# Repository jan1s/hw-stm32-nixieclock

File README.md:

# hw-nixieclock

The firmware running on the clock: [Firmware](https://github.com/jan1s/fw-clock)

A small Gist to configure a STM32 toolchain on Mac: [Toolchain](https://jan1s.github.io)

To flash the controller a STM32 Programmer is needed, just get the cheapest one from China.

## Initial Configuration

Before the clock will actually start working, it is necessary to set the type:

```bash
nixie_settype <type>
nixie_settype <type(0-4)>
```

Where `<type>` is a number defining the nixie clock type.

1. ZM1000
2. Z570M, IN-8
3. ZM1325
4. IN-14, ZM1020

It is also required to set the mode of operation:

```bash
nixie_setmode <mode>
nixie_setmode <mode(0=NONE|1=HHMMSS|2=HHMM|3=MMSS|4=YYYY)>
```

Where `<mode>` is a number defining the nixie operation mode.

1. HH:MM:SS
2. HH:MM
3. MM:SS
4. YYYY

## PCBs

The clock has seperate control and display pcbs. Those pcbs do not only form a basic case for the electronics, but also allow for flexible use with different tubes.

[Control PCBs](layout/control)

[Display PCBs](layout/display)

[Source PCBs](layout/source)

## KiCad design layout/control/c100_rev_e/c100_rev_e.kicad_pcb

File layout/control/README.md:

# Control PCBs

## c100

rev. a

In the first revision of the PCBs are some minor errors. (This is the version from the 32C3 workshop)
Find detailed pictures of the first prototype [here](../../docu/detail_c100_rev_a).

* A pullup resistor is missing on the USB data lines
* LED silkscreen missing, they are on the right of the controller

rev. b

## c150

rev. a

### control BOM
| Identifier | Type/Value | Quantity | [Reichelt][reichelt] | [Digikey][digikey] | Comment |
| :---        | :---        | :---      | :---         | :---      | :---     |
| R1, R2, R3, R4 | 33 Ω | 4 | SMD-0603 33 | 311-33GRCT-ND |
| R12, R13 | 1 kΩ | 2 | SMD-0603 1,00K | 311-1.0KGRCT-ND |
| C1, C2, C13, C14 | 10 pF | 4 | NPO-G0603 10P |  |
| C7, C8 | 10 nF | 2 | X7R-G0603 10N |  |
| C18, C19, C20, C21 | 100 nF | 4 | X7R-G0603 100N |  |
| C3, C5, C6, C10, C11 | 10 µF | 5 | X5R-G0603 10/6 |  |
| FB1 | Ferrite Bead | 1 | BLM18AG 121 | 490-1011-1-ND |
| Y1 | 8MHz | 1 | - | 535-10630-1-ND |
| Y2 | 32kHz | 1 | 32,768 PGD-9 | 535-9542-1-ND |
| LED1 | LED green | 1 | LG L29K |  |
| LED2 | LED white | 1 | LW L283 | |
| BAT1 | Batteryholder | 1 | - | BC501SM-ND | c100 |
| BAT1 | Batteryholder | 1 | KZH 20SMD-2 | - | c150 |
| BAT | CR 1220 | 1 | CR 1220 VAR | SY033-ND |
| SW1 | Tact Switch Top | 1 | - | EG2531CT-ND |
| J1 | 2x5 Socket | 1 | - | A100866TR-ND, S5714-ND |
| J2 | USB Jack | 1 | USB BWM SMD | 151-1206-1-ND |
| IC1 | STM32F103C8T6 | 1 | STM32 F103C8T6 | 497-6063-ND |
| IC2, IC6 | LP2985 | 1 | LP 2985 IM5-3,3 |  |
| IC3, IC4 | USBLC6-2 | 1 | - | 497-5235-1-ND |

### power supply BOM
| Identifier | Type/Value | Quantity | [Reichelt][reichelt] | [Digikey][digikey] | Comment |
| ---        | ---        | ---      | ---         | ---      | ---     |
| R23 | 0.01 Ω | 1 | - | RHM.10MCT-ND |
| R18 | 82 kΩ | 1 | SMD-0603 82K |  |
| R20 | 8,2 kΩ | 1 | SMD-0603 8,2K |  |
| R19 | 1 MΩ | 1 | SMD-1206 1M |  |
| C12 | 150 pF | 1 | NPO-G0603 150P |  |
| C9 | 22 nF | 1 | X7R-G0603 22N |  |
| C4 | 1 µF / 250V | 1 | 1u/250V | 490-3550-1-ND  | |
| C15, C16 | 10 µF | 2 | X5R-G0603 10/6 |  |
| C17 | 100 µF | 1 | X5R-G1210 100 |  |
| D2 | Diode | 1 | BAT 54C SMD |  |
| D3 | Diode | 1 | ES 2GA SMD |  |
| L2 | 680 µH | 1 | L-PISR 680µ |  |
| IC7 | IRF 7470 | 1 | IRF 7470 | IRF7470PBFCT-ND |
| IC5 | LT1619ES8 | 1 | - | LT1619ES8#PBF-ND |

[reichelt]: http://www.reichelt.de
[digikey]: http://www.digikey.de
[mouser]: http://mouser.com
[aliexpress]: http://www.aliexpress.com

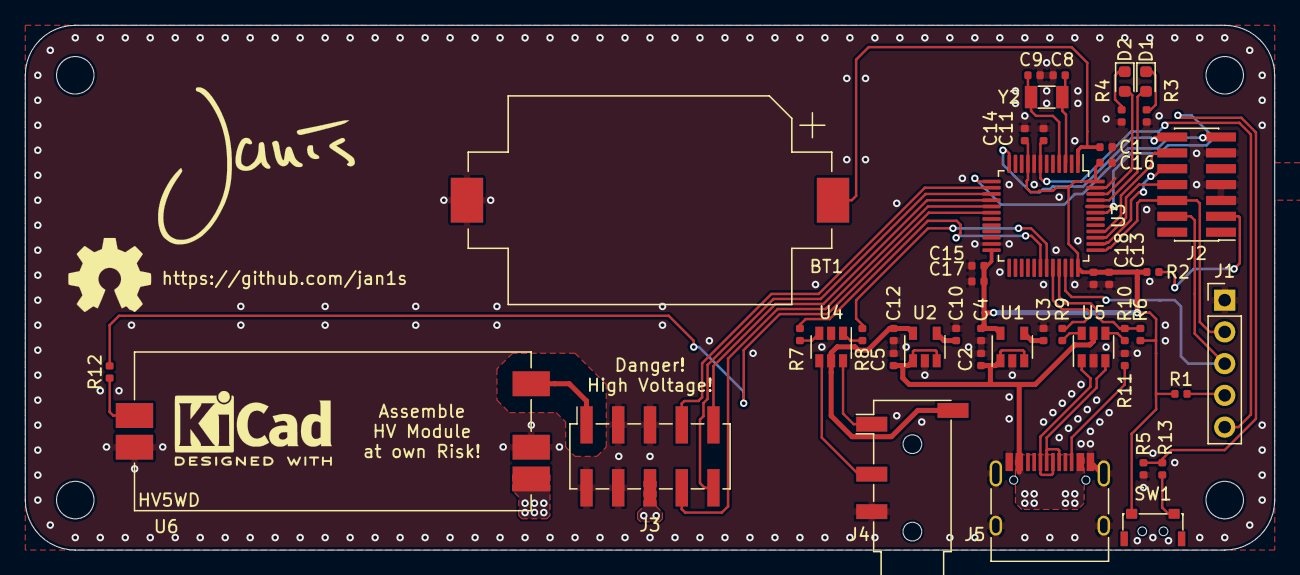
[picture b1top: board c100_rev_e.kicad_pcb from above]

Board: 2 copper layers, 100.0 x 42.0 mm, 45 parts (0 on the bottom side), 45 nets.

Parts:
BT1: Battery_Cell; BatteryHolder_Keystone_1060_1x2032
C1, C17: 1uF; C_0402_1005Metric
C2, C4, C5, C12, C13: 10uF; C_0402_1005Metric
C3, C10: 470pF; C_0402_1005Metric
C8, C9: 10p; C_0402_1005Metric
C11, C14, C15, C16, C18: 100nF; C_0402_1005Metric
D1, D2: LED White; LED_0603_1608Metric
J1: Conn_01x05; PinHeader_1x05_P2.54mm_Vertical
J2: STDC14; PinHeader_2x07_P1.27mm_Vertical_SMD
J3: Conn_02x05_Odd_Even; PinSocket_2x05_P2.54mm_Vertical_SMD
J4: AudioJack4_SwitchTR1; Jack_3.5mm_PJ320D_Horizontal
J5: USB_C_Receptacle_USB2.0; USB_C_Receptacle_HRO_TYPE-C-31-M-12
R1, R2, R5, R12: 10k; R_0402_1005Metric
R3, R4, R6: 1k5; R_0402_1005Metric
R7, R8, R9, R10, R13: 22R; R_0402_1005Metric
R11: 5k1; R_0402_1005Metric
SW1: SW_Push; 1TS003B
U1, U2: MIC5219-3.3YM5; SOT-23-5
U3: STM32F072C8Tx; LQFP-48_7x7mm_P0.5mm
U4, U5: USBLC6-2SC6; SOT-23-6
U6: HV5W; HV5W_SMD
Y2: 32.768kHz; Crystal_SMD_3215-2Pin_3.2x1.5mm

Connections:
+3.3V_TRS: C12.1, J4.S, U2.5, U4.5
+3V3: C4.1, C13.1, C14.1, C15.1, C16.1, C17.1, C18.1, R1.1, R2.1, R6.2, SW1.2, U1.5, U3.9, U3.24, U3.36, U3.48
+5V: C2.1, C5.1, J3.6, J5.A4, J5.A9, J5.B4, J5.B9, U1.1, U1.3, U2.1, U2.3, U5.5, U6.1
+170V: J3.1, U6.5
+BATT: BT1.1, C1.1, U3.1
BTN: R5.1, R13.1, U3.43, U3.44
GND: BT1.2, C1.2, C2.2, C3.2, C4.2, C5.2, C8.2, C9.2, C10.2, C11.1, C12.2, C13.2, C14.2, C15.2, C16.2, C17.2, C18.2, J1.1, J2.5, J2.7, J2.11, J3.2, J3.3, J3.4, J3.5, J4.R2, J5.A1, J5.A12, J5.B1, J5.B12, J5.S1, R3.2, R4.2, R5.2, R11.2, U1.2, U2.2, U3.8, U3.23, U3.35, U3.47, U4.2, U5.2, U6.3, U6.4
HV_EN: R12.2, U3.18
NX_EN: J3.7, U3.14
NX_RCK: J3.9, U3.16
unnamed: C3.1, U1.4
unnamed: C8.1, U3.3, Y2.2
unnamed: C9.1, U3.4, Y2.1
unnamed: C10.1, U2.4
unnamed: D1.1, R3.1
unnamed: D1.2, U3.45
unnamed: D2.1, R4.1
unnamed: D2.2, U3.46
unnamed: J1.4, R1.2
unnamed: J2.3, R2.2
unnamed: J4.R1, U4.4
unnamed: J4.T, U4.6
unnamed: J5.A6, J5.B6, U5.3
unnamed: J5.A7, J5.B7, U5.1
unnamed: J5.B5, R11.1
unnamed: R7.1, U3.30
unnamed: R7.2, U4.3
unnamed: R8.1, U3.31
unnamed: R8.2, U4.1
unnamed: R9.1, U3.32
unnamed: R9.2, U5.6
unnamed: R6.1, R10.1, U3.33
unnamed: R10.2, U5.4
unnamed: R12.1, U6.2
unnamed: R13.2, SW1.1
RST: C11.2, J1.5, U3.7
SPI1_MOSI: J3.8, U3.17
SPI1_SCK: J3.10, U3.15
T_JTDI: J2.10, U3.38
T_JTDO: J2.8, U3.39
T_NRST: J2.12, U3.40
T_SWCLK: J1.2, J2.6, U3.37
T_SWDIO: J1.3, J2.4, U3.34
T_VCP_RX: J2.13, U3.13
T_VCP_TX: J2.14, U3.12

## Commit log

2015-11-17 Added control pcb render
2015-11-17 Added case
2015-11-17 Added BT timesource
2015-12-08 Added BOM list
2015-12-08 Fixed values
2015-12-30 Fixes in case
2015-12-31 Fixed display bug
2016-01-02 Changed structure, added HM-11
2016-01-03 Changed structure, added c150 and c200
2016-01-03 C100 production ready
2016-01-03 Finished c150 rev a
2016-01-03 Added control pcb readme
2016-01-03 Added display readme
2016-01-03 Fixed readme
2016-01-13 Added detail of c100, d100 rev a bodges
2016-01-13 Revert "Added detail of c100, d100 rev a bodges"
    This reverts commit f08b87db82e6815f0eeb61e454d55ffe807eec73.
2016-01-13 Added detail of rev a bodges
2016-01-14 Added Readme
2016-01-17 Fixed naming
2016-12-18 Added ESP-12
2016-12-18 Added final c200 production files
2016-12-29 Added Wifi Module
2017-02-11 Fixed RX/TX
2017-09-01 Added updated wifi source
2017-10-22 Added rev. B, Fixed connector distance...
2017-11-01 Added rev. B of large clock layouts
2018-01-07 Added new control board versions and TRS adapter
2018-08-03 Added new c150 board
2018-08-03 C200 missing..
2018-08-03 Added HV module
2020-02-05 Added c100_rev_e
